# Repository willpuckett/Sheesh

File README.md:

# 🍁 Sheesh

> _Sheesh_ is a tiny board to celebrate the coming of 🍂 with minimal finger
> travel.

After spending the day at my computer, I stepped out with friends Saturday night
for a burger & beverage. On the patio of our local institution, the air was
cool.

> _Autumn had undeniably arrived._

I had been wanting to squeeze a Ferris Sweep out of a Xiao somehow and it
occurred to me as I later continued working that maybe I was actually trying to
make a 28 key keyboard. When I started searching for a board outline, I reached
for a leaf to lay over the keys. I choose a maple leaf both for the aesthetic
quality with which the keys fit, and for the pleasant memories of eating maple
butter in Montreal's Jean-Talon Market it conjured.

> [!NOTE] 
> _Sheesh_ honors the Ojibway people, who (according to the interwebs)
> call maple _sheesheegummavvis_: “sap flows fast."

The size of the Xiao makes it so attractive for smaller keyboards. _Sheesh_
intended to repurpose the reset and nfc pins to squeeze enough I/O to directly
connect the 28 keys. Unfortunately, coopting the reset pin didn't work well,
although the initial exploration revealed a lot more chording opportunities. It
seems to make more sense to explore a 26 key layout in another board, so version
0.2 and up switch to a diode layout. _Sheesh_ is an exploration in PCBA, and
uses 0402 diodes which are not conducive to handsoldering.

> [!IMPORTANT]
> If you have time, please drop a note to your local Seeed representative asking
> that they via the PDM pins (pins 0.16, 1.0, and 1.10) to pads on the underside
> of Xiao nRF52840. [[Seeed USA](mailto:seeed_us@seeed.cc)]
> [[Seeed Europe](mailto:seeed_emea@seeed.cc)]

## BOM

|      QTY      |            Part            | JLCPCB Part # |
| :-----------: | :------------------------: | :-----------: |
|       2       |     BAT-SMD_MY-LR44-02     |   C2902345    |
|       2       |         SSSS811101         |    C109335    |
|       4       |     MF254V-11-07-0743      |   C2889988    |
|       8       |       YZ00615050R-04       |   C5157400    |
| 56 (optional) |  3305-0-15-80-47-27-10-0   |   C17370797   |
|      28       | ChocV1 switches (Red Pros) |      N/A      |
|       2       |  3.7V LIR1254 (NOT LR44!)  |      N/A      |

## Putting it Together

### Fabrication & Assembly Files [[zip](https://github.com/willpuckett/Sheesh/releases/latest/download/jlcpcb.zip)]

For the love of god and country 🇨🇦, please have this fabricated with red mask
and white silk.

> [!CAUTION]
> Use 3.7v LIR1254 (lithium ion rechargable) battery **only**.

## Case

### There's a case [[step](https://github.com/willpuckett/Sheesh/releases/latest/download/case.step)] [[stl](https://github.com/willpuckett/Sheesh/releases/latest/download/case.step)]

It's really more of a skin. Print and place the pcb directly in it. Red or white
TPU is ideal... The case is only one half, flip it in your slicer for the other
half 🙃

> [!TIP]
> Polymaker TPU works well. It seems to like to print slow and cool—leave the
> door open.

TPU is relatively non-slip, absorbing and distributing the force of typing very
nicely. No bumpons required.

## Layouts

Download the latest ZMK Builds.

### Engrammer  [[left](https://github.com/willpuckett/Sheesh/releases/latest/download/sheesh_engrammer_left.uf2)] [[right](https://github.com/willpuckett/Sheesh/releases/latest/download/sheesh_engrammer_right.uf2)] 

## Pre Fabs

The extras will be [available](https://octule.com) when they arrive if you don't
want to have to deal with a minimum order...

## Writing Your Own Keymap

Should you not be prepared for engrammer, you can easily make your own keymap
that references the sheesh shield...

> [!TIP]
> Don't feel like going through the below steps? Unpack
> [this zip](https://github.com/willpuckett/sheesh/config/zmk-config.zip), edit,
> and push to your github account to build.

1. Init a new ZMK repo `bash -c "$(curl -fsSL https://zmk.dev/setup.sh)"`
2. Type `1` to select a keyboard
3. Type `22` to select Seeeduino XIAO BLE
4. Type `Y` to copy in a stock keymap
5. Ender your github username so you can push your config to build it
6. Type `Y` to execute it
7. You can delete the `boards` and `zephyr` directories to keep things tidy
8. In `build.yaml`, change the `shield` to `sheesh`
9. In the config directory, rename the `.conf` and `.keymap` files to `sheesh`,
   keeping their respective `.conf` and `.keymap` extensions it should look like
   this:

```bash
❯ ls --tree zmk-config/config
config
├── sheesh.conf
├── sheesh.keymap
└── west.yml
```

10. In the same directory, edit `west.yml` to look like this:

```yaml
manifest:
  remotes:
    - name: zmkfirmware
      url-base: https://github.com/zmkfirmware
    # Additional modules containing boards/shields/custom code can be listed here as well
    # See https://docs.zephyrproject.org/3.2.0/develop/west/manifest.html#projects
    - name: willpuckett
      url-base: https://github.com/willpuckett
  projects:
    - name: zmk
      remote: zmkfirmware
      revision: main
      import: app/west.yml
    - name: sheesh
      remote: willpuckett
      repo-path: sheesh/config
      revision: main
  self:
    path: config
```

11. Edit `config/sheesh.keymap`. You can start by copying in one of the
    [layers from this file](https://github.com/willpuckett/sheesh/config/boards/shields/sheesh/sheesh.keymap)
    as a starting point. Then push the folder to your github to build in an
    action.

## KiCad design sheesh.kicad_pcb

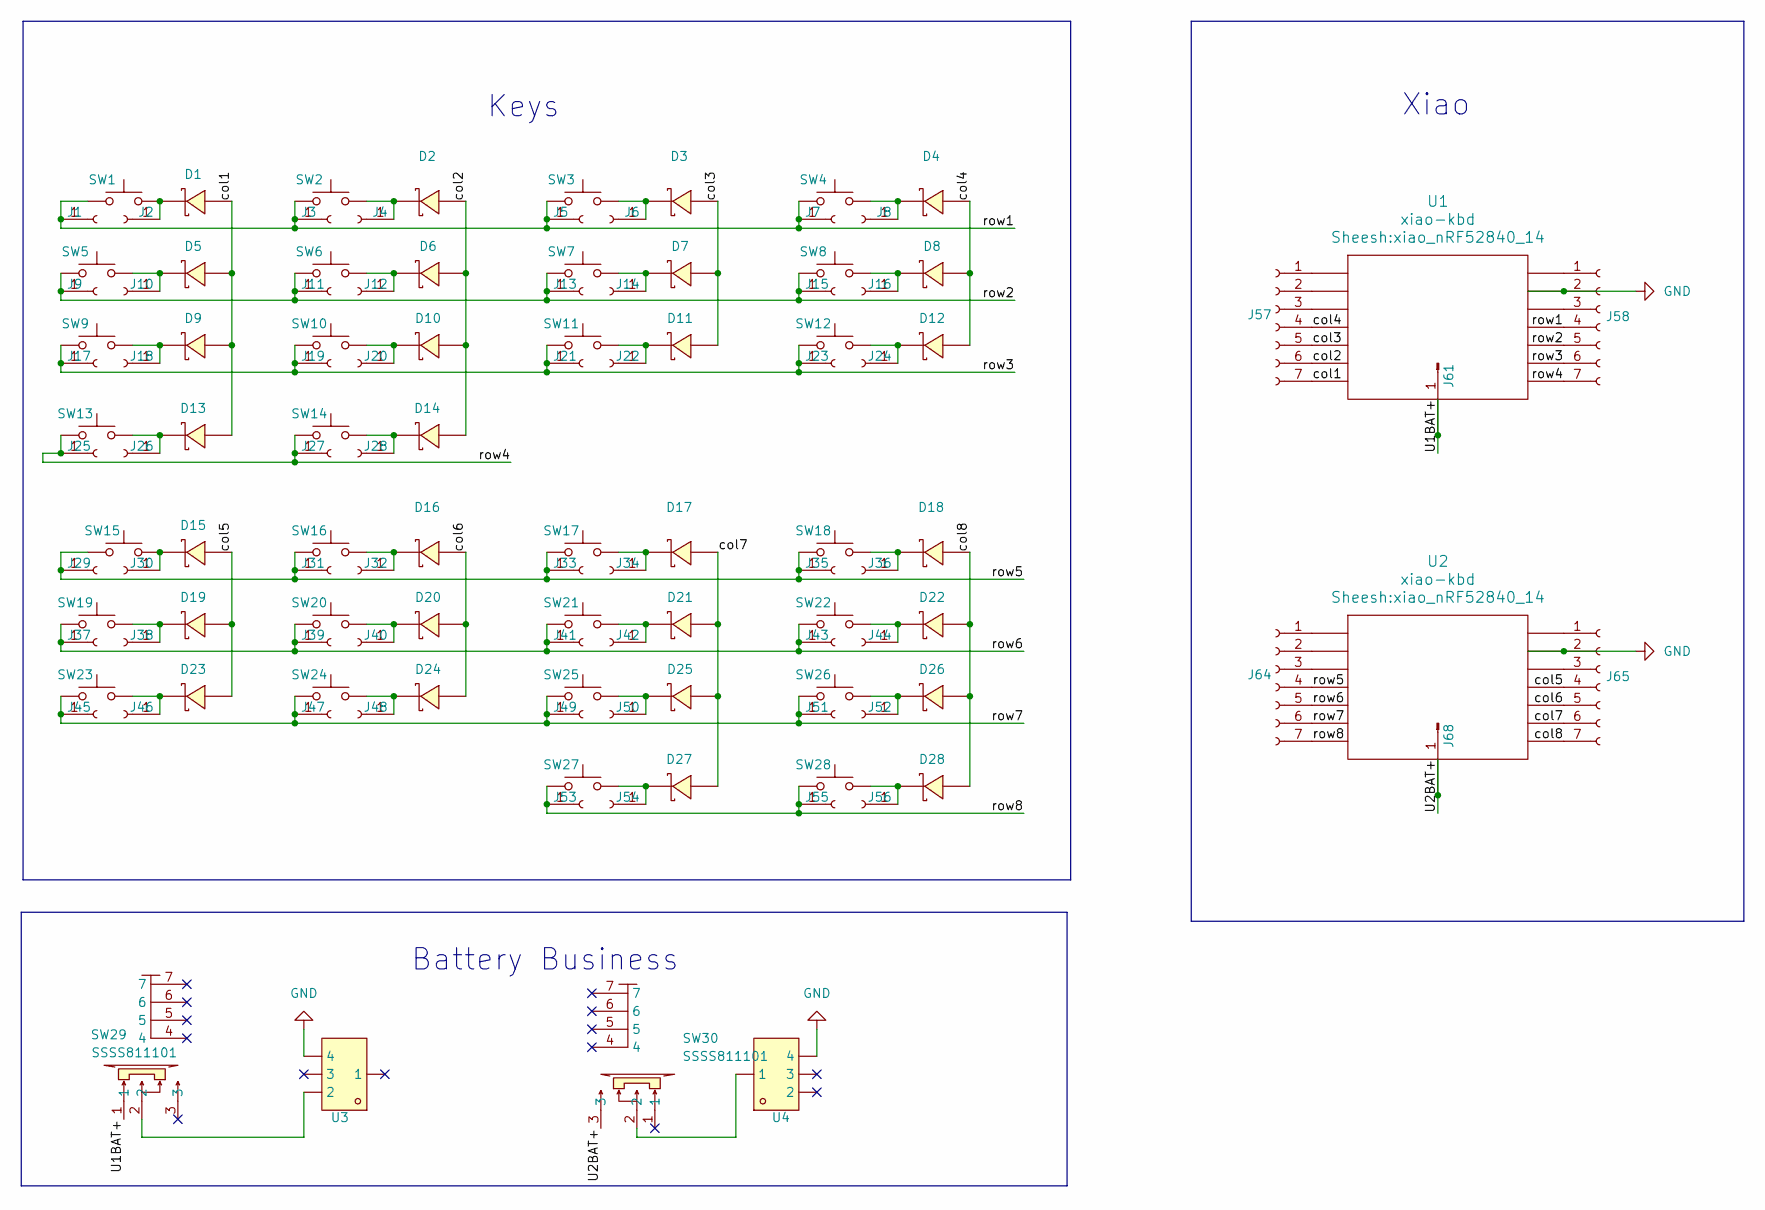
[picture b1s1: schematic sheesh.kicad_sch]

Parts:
D1, D2, D3, D4, D5, D6, D7, D8, D9, D10, D11, D12, D13, D14, D15, D16, D17, D18, D19, D20, D21, D22, D23, D24, D25, D26, D27, D28: CDSQC4148-HF; X1-DFN1006-2_L1.0-W0.6-RD; LCSC C6341459
J1, J2, J3, J4, J5, J6, J7, J8, J9, J10, J11, J12, J13, J14, J15, J16, J17, J18, J19, J20, J21, J22, J23, J24, J25, J26, J27, J28, J29, J30, J31, J32, J33, J34, J35, J36, J37, J38, J39, J40, J41, J42, J43, J44, J45, J46, J47, J48, J49, J50, J51, J52, J53, J54, J55, J56: 3305-0-15-80-47-27-10-0; MPN 3305-0-15-80-47-27-10-0; LCSC C17370797
J57, J58, J64, J65: MF254V-11-07-0743; MPN 310-13-107-41-001000; LCSC C2889988
J61, J68: YZ00615050R-04; MPN 0906-2-15-20-75-14-11-0; LCSC C5157400
SW1, SW2, SW3, SW4, SW5, SW6, SW7, SW8, SW9, SW10, SW11, SW12, SW13, SW14, SW15, SW16, SW17, SW18, SW19, SW20, SW21, SW22, SW23, SW24, SW25, SW26, SW27, SW28: SW_Push; SW_PG1350
SW29, SW30: SSSS811101; SW-SMD_SSSS811101; LCSC C109335
U1, U2: xiao-kbd; xiao_nRF52840_14
U3, U4: MY-LR44-02; BAT-SMD_MY-LR44-02; MPN MY-LR44-02; LCSC C2902345

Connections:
/U1BAT+: J61.1, SW29.1, U1.17 (BAT+)
/U2BAT+: J68.1, SW30.3, U2.17 (BAT+)
/col1: D1.2 (A), D5.2 (A), D9.2 (A), D13.2 (A), J57.7, U1.7 (D6)
/col2: D2.2 (A), D6.2 (A), D10.2 (A), D14.2 (A), J57.6, U1.6 (D5)
/col3: D3.2 (A), D7.2 (A), D11.2 (A), J57.5, U1.5 (D4)
/col4: D4.2 (A), D8.2 (A), D12.2 (A), J57.4, U1.4 (D3)
/col5: D15.2 (A), D19.2 (A), D23.2 (A), J65.4, U2.11 (D10)
/col6: D16.2 (A), D20.2 (A), D24.2 (A), J65.5, U2.10 (D9)
/col7: D17.2 (A), D21.2 (A), D25.2 (A), D27.2 (A), J65.6, U2.9 (D8)
/col8: D18.2 (A), D22.2 (A), D26.2 (A), D28.2 (A), J65.7, U2.8 (D7)
/row1: J1.1, J3.1, J5.1, J7.1, J58.4, SW1.1, SW2.1, SW3.1, SW4.1, U1.11 (D10)
/row2: J9.1, J11.1, J13.1, J15.1, J58.5, SW5.1, SW6.1, SW7.1, SW8.1, U1.10 (D9)
/row3: J17.1, J19.1, J21.1, J23.1, J58.6, SW9.1, SW10.1, SW11.1, SW12.1, U1.9 (D8)
/row4: J25.1, J27.1, J58.7, SW13.1, SW14.1, U1.8 (D7)
/row5: J29.1, J31.1, J33.1, J35.1, J64.4, SW15.1, SW16.1, SW17.1, SW18.1, U2.4 (D3)
/row6: J37.1, J39.1, J41.1, J43.1, J64.5, SW19.1, SW20.1, SW21.1, SW22.1, U2.5 (D4)
/row7: J45.1, J47.1, J49.1, J51.1, J64.6, SW23.1, SW24.1, SW25.1, SW26.1, U2.6 (D5)
/row8: J53.1, J55.1, J64.7, SW27.1, SW28.1, U2.7 (D6)
GND: J58.2, J65.2, U1.13 (GND), U2.13 (GND), U3.4, U4.4
unnamed: D1.1 (K), J2.1, SW1.2
unnamed: D2.1 (K), J4.1, SW2.2
unnamed: D3.1 (K), J6.1, SW3.2
unnamed: D4.1 (K), J8.1, SW4.2
unnamed: D5.1 (K), J10.1, SW5.2
unnamed: D6.1 (K), J12.1, SW6.2
unnamed: D7.1 (K), J14.1, SW7.2
unnamed: D8.1 (K), J16.1, SW8.2
unnamed: D9.1 (K), J18.1, SW9.2
unnamed: D10.1 (K), J20.1, SW10.2
unnamed: D11.1 (K), J22.1, SW11.2
unnamed: D12.1 (K), J24.1, SW12.2
unnamed: D13.1 (K), J26.1, SW13.2
unnamed: D14.1 (K), J28.1, SW14.2
unnamed: D15.1 (K), J30.1, SW15.2
unnamed: D16.1 (K), J32.1, SW16.2
unnamed: D17.1 (K), J34.1, SW17.2
unnamed: D18.1 (K), J36.1, SW18.2
unnamed: D19.1 (K), J38.1, SW19.2
unnamed: D20.1 (K), J40.1, SW20.2
unnamed: D21.1 (K), J42.1, SW21.2
unnamed: D22.1 (K), J44.1, SW22.2
unnamed: D23.1 (K), J46.1, SW23.2
unnamed: D24.1 (K), J48.1, SW24.2
unnamed: D25.1 (K), J50.1, SW25.2
unnamed: D26.1 (K), J52.1, SW26.2
unnamed: D27.1 (K), J54.1, SW27.2
unnamed: D28.1 (K), J56.1, SW28.2
unnamed: J57.1, U1.1 (D0)
unnamed: J57.2, U1.2 (D1)
unnamed: J57.3, U1.3 (D2)
unnamed: J58.1, U1.14 (5v)
unnamed: J58.3, U1.12 (3v3)
unnamed: J64.1, U2.1 (D0)
unnamed: J64.2, U2.2 (D1)
unnamed: J64.3, U2.3 (D2)
unnamed: J65.1, U2.14 (5v)
unnamed: J65.3, U2.12 (3v3)
unnamed: SW29.2, U3.2
unnamed: SW30.2, U4.1

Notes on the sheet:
Battery Business
Keys
Xiao

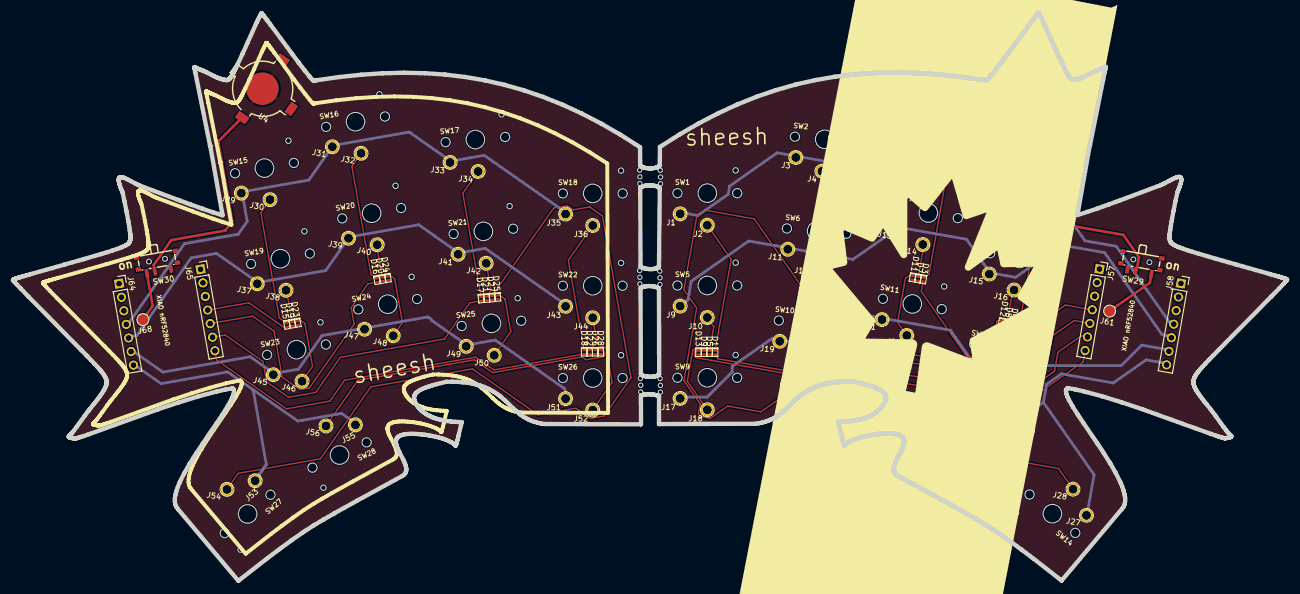
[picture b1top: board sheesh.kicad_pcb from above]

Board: 2 copper layers, 234.7 x 104.6 mm, 124 parts (0 on the bottom side), 59 nets.

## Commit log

2024-09-26 ignore erc error
2024-09-27 fix(sw-th_ssss811101): swap SW29 & SW30 symbol & footprint
    Change PCM12SMTR to SSSS811101. The latter fits on the former's footprint, but the location was
    slightly off fin the cpl
2024-09-27 fix(component): correct lcsc field name on ssss811101
    correct lcsc field name so it passes kibot filter
2024-09-27 style(component): nudge switch away from pogo pin
    nudge power switch for more comfortable clearance
2024-09-27 docs(readme.md): add etsy link
    Link to prefab keyboards
2024-09-27 fix(pcb): add space between potential shorts
    slightly adjust further recently updated switches and pogo pins to reduce the chance of failure
2024-09-27 add module yaml for use in other configs, zmk-config template, and instructions to readme
2024-09-27 chore(settings.json): purge settings.json
    .vscode/settings.json was a leftover and served no purpose
2024-10-03 change module location and template
2024-10-03 feat(sheesh.keymap): add combos
2024-10-03 fix(sheesh.keymap): fix typo
    add missing # to directive
2024-10-03 fix(sheesh.keymap): change directive
    switch to elif from elseif
2024-10-03 feat(keymap.yml): run only on success
    add conditional to workflow run to only run on successful completion
2024-10-13 add bootloader to keymap
2024-10-14 try setting reset pin in conf option, correct pin numbers on right half
2024-10-20 move behaviors to seperate files
2024-10-20 correct includes
2024-10-20 remove labels
2024-10-20 correct .confs
2024-10-20 remove qwerty
2024-10-20 add require-prior-idle-ms
2024-10-20 checking nreset
2024-10-20 config nfc with uicr
2024-10-21 switch to diodes
2024-10-21 clean up switch to diodes
2024-10-21 remove subrepo
2024-10-21 refill zones
2024-10-21 remove switch back silk
2024-10-21 correct keymap
2024-10-21 correct diode text and part number
2024-10-21 remove deprecated silks
2024-10-21 remove bootloader key
2024-10-21 correct typo
2024-10-21 remove mousebites from position file
2024-10-21 remove deprecated silk
2024-10-21 add installation documentation
